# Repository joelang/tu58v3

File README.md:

# tu58v3
Improved version of tu58 emulator

This is an emulator for a DEC TU-58 block addressable tape system. 

It is wrtten in AVR assembler. 

This project has been ongoing for many years. On the back burner. A few years back
I got the rom image from a real TU-58. I disassembled and commented the code.
(It's on bitsavers) That gave me an outline for my AVR code.

The storage is a single CF card that supports multiple images of 65536 512 byte blocks.
This is far more storage than a real TU-58 could support. 

Some things are different from a real TU-58:

BLOCKS greater than 512 supported

No capstan roller to turn to goo

Boot switch not implemented

Special addressing mode not implemented.

The emulator has been tested with RT-11 and XXDP test CZTUU.

I have done a PCB layout and had prototypes run (OSHPARK)

This is an updated version of the tu-58 emulator

The processor has been changed to an ATmega32A to allow a parallel interface to the CF card.

Component count is reduced by eliminating the SPI interface.

Jumpers have been added to select baud rate.

UNIT is restricted to 0 or 1 to prevent corrupting CF card image.

JTAG programming and test connector added.

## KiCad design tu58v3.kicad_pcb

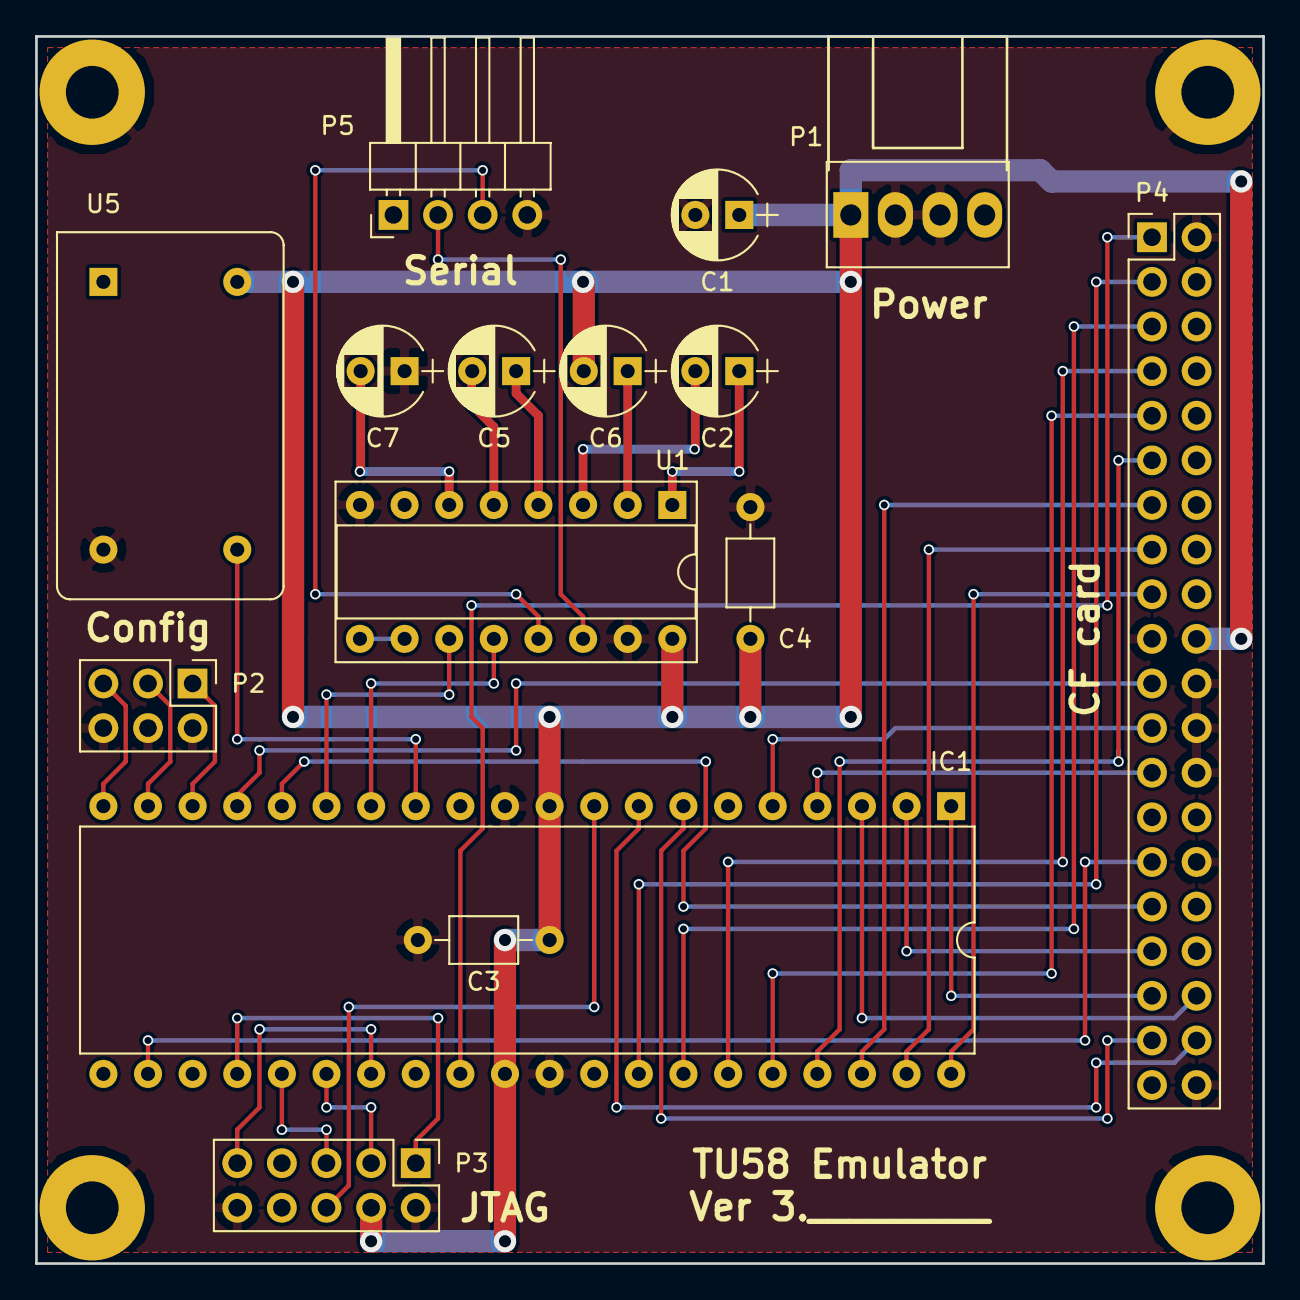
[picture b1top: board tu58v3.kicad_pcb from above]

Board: 2 copper layers, 69.9 x 69.9 mm, 19 parts (0 on the bottom side), 41 nets.

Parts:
C1, C2, C5, C6, C7: 10uf; CP_Radial_D5.0mm_P2.50mm
C3, C4: .1uf; C_Axial_L3.8mm_D2.6mm_P7.50mm_Horizontal
IC1: ATMEGA32A-P; DIP-40_W15.24mm
MH1, MH2, MH3, MH4: CONN_01X01; MountingHole_3mm_Pad
P1: CONN_01X04; FDC-4P-RA
P2: CONN_02X03; Pin_Header_Straight_2x03_Pitch2.54mm
P3: CONN_02X05; Pin_Header_Straight_2x05_Pitch2.54mm
P4: CONN_02X20; Pin_Header_Straight_2x20_Pitch2.54mm
P5: CONN_01X04; Pin_Header_Angled_1x04_Pitch2.54mm
U1: MAX232; DIP-16_W7.62mm_Socket
U5: OSC 11.0592MHz.; Oscillator_DIP-14

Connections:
A0: IC1.1, P4.35
A1: IC1.2, P4.33
A2: IC1.3, P4.36
CF_ACK: IC1.22, P4.29
CF_CS: IC1.7, P4.37
CF_CSX: IC1.8, P4.38
CF_DRQ: IC1.17, P4.21
CF_IRQ: IC1.16, P4.31
D0: IC1.40, P4.17
D1: IC1.39, P4.15
D2: IC1.38, P4.13
D3: IC1.37, P4.11
D4: IC1.36, P4.9
D5: IC1.35, P4.7
D6: IC1.34, P4.5
D7: IC1.33, P4.3
GND: C1.2, C3.2, C4.2, C7.1, IC1.11, IC1.31, MH1.1, MH2.1, MH3.1, MH4.1, P1.2, P1.3, P2.2, P2.4, P2.6, P3.2, P3.10, P4.2, P4.19, P4.22, P4.24, P4.26, P4.30, P4.40, P5.4, U1.8, U1.15, U5.7
IOR: IC1.4, P4.25
IOW: IC1.5, P4.23
unnamed: C2.1, U1.1
unnamed: C2.2, U1.3
unnamed: C5.1, U1.4
unnamed: C5.2, U1.5
unnamed: C6.1, U1.2
unnamed: C7.2, U1.6
unnamed: IC1.9, P3.6
unnamed: IC1.13, U5.8
unnamed: IC1.14, U1.12
unnamed: IC1.15, U1.11
unnamed: IC1.18, P2.1
unnamed: IC1.19, P2.3
unnamed: IC1.20, P2.5
unnamed: IC1.24, P3.1
unnamed: IC1.25, P3.5
unnamed: IC1.26, P3.3
unnamed: IC1.27, P3.9
unnamed: P5.2, U1.14
unnamed: P5.3, U1.13
unnamed: U1.9, U1.10
RST: IC1.29, P4.1
VCC: C1.1, C3.1, C4.1, C6.2, IC1.10, IC1.30, P1.1, P3.4, P4.20, U1.16, U5.14

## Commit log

2019-08-17 Update README.md
    edit typo
